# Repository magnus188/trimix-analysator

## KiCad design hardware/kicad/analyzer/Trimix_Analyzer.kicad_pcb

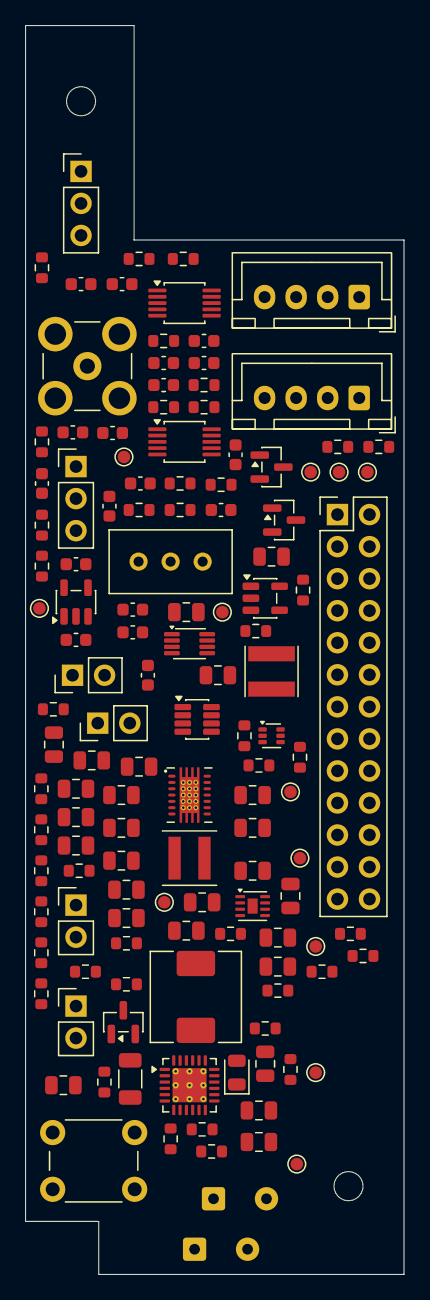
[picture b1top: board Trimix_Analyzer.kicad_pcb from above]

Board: 4 copper layers, 30.0 x 99.0 mm, 133 parts (0 on the bottom side), 67 nets, no tracks yet.

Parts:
C101: 1u / 25V X7R; C_0805_2012Metric
C102: 10u / 25V X7R; C_1206_3216Metric
C103: 47n / 16V X7R; C_0805_2012Metric
C104, C105, C204, C205, C206: 22u / 10V X7R; C_0805_2012Metric
C106, C201, C202: 10u / 10V X7R; C_0805_2012Metric
C107: 4.7u / 10V X7R; C_0805_2012Metric
C203, C301: 100n / 10V X7R; C_0805_2012Metric
C401, C404, C408, C409, C505, C509: 1u / X7R; C_0603_1608Metric
C402, C403, C405, C406, C503, C506, C507: 10n; C_0603_1608Metric
C407, C504, C508: 100n; C_0603_1608Metric
C501, C502: 4.7u / X7R / 10V; C_0603_1608Metric
C601, C804: 1u / 10V; C_0805_2012Metric
C701: 10u / 10V; C_0805_2012Metric
C702, C703: 22u / 10V; C_0805_2012Metric
C704, C705: 4.7u / 10V; C_0805_2012Metric
C706: 10n; C_0805_2012Metric
C707, C708: 100n; C_0805_2012Metric
C801, C802: 100n / 10V; C_0805_2012Metric
C803: 33n / 10V; C_0805_2012Metric
D101: CHARGE (red); LED_0805_2012Metric
H1, H2: M2 NPTH 2.30; Mechanical_M2_NPTH_2.30mm
J101: FROM USB BOARD (2P); SolderWire-0.25sqmm_1x02_P4.2mm_D0.65mm_OD1.7mm
J102: PACK PIGTAIL; SolderWire-0.25sqmm_1x02_P4.2mm_D0.65mm_OD1.7mm
J103: PACK NTC: 103AT-2; PinHeader_1x02_P2.54mm_Vertical
J104: ARM: OPEN; PinHeader_1x02_P2.54mm_Vertical
J301: GUITION JP1 / 2x13; PinHeader_2x13_P2.54mm_Vertical
J401: AO2 / 3-pin cable; PinHeader_1x03_P2.54mm_Vertical
J402: SMB Male PCB / verify fit; SMB_Jack_Vertical
J501: MD62 cable / <=30 cm; PinHeader_1x03_P2.54mm_Vertical
J601: BME280 harness; JST_XH_B4B-XH-A_1x04_P2.50mm_Vertical
J701: ZE07-CO harness; JST_XH_B4B-XH-A_1x04_P2.50mm_Vertical
J801: POWER BUTTON / 1NO; PinHeader_1x02_P2.54mm_Vertical
J802: BUTTON LED +/-; PinHeader_1x02_P2.54mm_Vertical
L101: 1u / Isat >= 4.5A; L_Wuerth_HCM-7050
L201: 1.5u / XFL4020-152ME; L_Coilcraft_XxL4020
L701: 1uH / Isat >= 5 A; L_Taiyo-Yuden_NR-40xx
Q101: 2N7002; SOT-23
Q601, Q602: BSS138; SOT-23
R101: 5.23k 1%; R_0603_1608Metric
R102: 30.1k 1%; R_0603_1608Metric
R103: 620R 1%; R_0603_1608Metric
R104, R105, R203, R501, R703, R803: 100k; R_0603_1608Metric
R106: 2.2k; R_0603_1608Metric
R107, R301, R802: 10k; R_0603_1608Metric
R201: 1.62M 1%; R_0603_1608Metric
R202: 180k 1%; R_0603_1608Metric
R302, R303: 4.7k / FIT; R_0603_1608Metric
R401, R402, R405, R406, R506, R507: 100R / 0.1%; R_0603_1608Metric
R403, R404, R407, R408: 1M / 1%; R_0603_1608Metric
R409, R410, R504, R505: 10k / 0.1%; R_0603_1608Metric
R502, R503: 2k / 0.1%; R_0603_1608Metric
R601: 0R / fit: 3.3 V; R_0603_1608Metric
R602: 0R / DNP: 5 V option; R_0603_1608Metric
R603, R604: 4.7k / DNP; R_0603_1608Metric
R701: 787k / 0.1%; R_0603_1608Metric
R702: 100k / 0.1%; R_0603_1608Metric
R704, R705: 100R; R_0603_1608Metric
R801: 5.1k; R_0603_1608Metric
R804: 1k / DNP; R_0603_1608Metric
RV501: 500R / multiturn; Potentiometer_Bourns_3296W_Vertical
SW101: BQ wake / reset; SW_PUSH_6mm
TP1001: GND; TestPoint_Pad_D1.0mm
TP1002: USB_5V; TestPoint_Pad_D1.0mm
TP1003: PACK_P; TestPoint_Pad_D1.0mm
TP1004: VSYS; TestPoint_Pad_D1.0mm
TP1005: VOUT_5V; TestPoint_Pad_D1.0mm
TP1006: HOST_3V3; TestPoint_Pad_D1.0mm
TP1007: POWER_EN; TestPoint_Pad_D1.0mm
TP1008: I2C_SCL; TestPoint_Pad_D1.0mm
TP1009: I2C_SDA; TestPoint_Pad_D1.0mm
TP1010: HE_3V0; TestPoint_Pad_D1.0mm
TP1011: HE_SENSE; TestPoint_Pad_D1.0mm
TP1012: O2_VMID; TestPoint_Pad_D1.0mm
U101: BQ25895RTWR; Texas_RTW_WQFN-24-1EP_4x4mm_P0.5mm_EP2.7x2.7mm_ThermalVias
U201: TPS63020DSJR; TI_DSJ_14
U301: MAX17048G+; TDFN-8-1EP_2x2mm_P0.5mm_EP0.8x1.2mm
U401, U502: ADS1115IDGS; TSSOP-10_3x3mm_P0.5mm
U501, U702: SPX3819M5-L-3-0; SOT-23-5
U701: TPS61023DRLR; SOT-563
U703: TXU0202DCUR; VSSOP-8_2.3x2mm_P0.5mm
U801: LTC2954CTS8-1; TSOT-23-8

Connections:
/01 CHARGING + BATTERY/BQ_BTST: C103.2, U101.21
/01 CHARGING + BATTERY/BQ_ILIM: R103.1, U101.10
/01 CHARGING + BATTERY/BQ_PMID: C102.1, U101.23
/01 CHARGING + BATTERY/BQ_QON_N: SW101.1, U101.12
/01 CHARGING + BATTERY/BQ_REGN: C107.1, R101.1, U101.22
/01 CHARGING + BATTERY/BQ_SW: C103.1, L101.1, U101.19, U101.20
/01 CHARGING + BATTERY/CHG_CE_N: Q101.3, R104.2, U101.9
/01 CHARGING + BATTERY/CHG_STAT_N: D101.1, U101.4
/01 CHARGING + BATTERY/PACK_TS: J103.1, R101.2, R102.1, U101.11
/02 SWITCHED 5 V/TPS_FB: R201.2, R202.1, U201.3
/02 SWITCHED 5 V/TPS_VINA: C203.1, U201.1
BME_SCL: J601.3, Q601.3, R603.2
BME_SDA: J601.4, Q602.3, R604.2
BME_VIN: C601.1, J601.1, R601.2, R602.2, R603.1, R604.1
BUTTON_LED_A: J802.1, R804.2
CHARGE_ARM: J104.2, Q101.1, R105.1
CHG_INT_N: J301.13, R107.2, U101.7
CO_5V28: C702.1, C703.1, J701.1, R701.1, U701.6
CO_FB: R701.2, R702.1, U701.1
CO_LOGIC_3V0: C705.1, C708.1, U702.5, U703.7
CO_LOGIC_BYP: C706.1, U702.4
CO_RX_3V0: R705.1, U703.8
CO_RX_CABLE: J701.4, R705.2
CO_SW: L701.2, U701.5
CO_TX_3V0: R704.1, U703.1
CO_TX_CABLE: J701.3, R704.2
CO_UART_EN: J301.9, R703.1, U703.6
CO_UART_RX: J301.10, U703.4
CO_UART_TX: J301.12, U703.5
GAUGE_ALERT_N: J301.11, R301.2, U301.5
GND: C101.2, C102.2, C104.2, C105.2, C106.2, C107.2, C201.2, C202.2, C203.2, C204.2, C205.2, C206.2, C301.2, C402.2, C403.2, C405.2, C406.2, C407.2, C408.2, C409.2, C501.2, C502.2, C503.2, C504.2, C506.2, C507.2, C508.2, C509.2, C601.2, C701.2, C702.2, C703.2, C704.2, C705.2, C706.2, C707.2, C708.2, C801.2, C802.2, C803.2, C804.2, J101.2, J102.2, J103.2, J301.5, J301.6, J301.16, J501.3, J601.2, J701.2, J801.2, J802.2, Q101.2, R102.2, R103.2, R105.2, R202.2, R410.2, R501.2, R503.2, R505.2, R702.2, R703.2, SW101.2, TP1001.1, U101.8, U101.17, U101.18, U101.25, U201.2, U201.15, U301.1, U301.4, U301.6, U301.9, U401.1, U401.3, U501.2, U502.3, U701.4, U702.2, U703.2, U801.4
HE_3V0: C502.1, J501.1, R502.1, R504.1, TP1010.1, U501.5
HE_AIN_N: C505.2, C507.1, R507.2, U502.5
HE_AIN_P: C505.1, C506.1, R506.2, U502.4
HE_ENABLE: J301.17, R501.1, U501.3
HE_EXC_DIV: C504.1, R504.2, R505.1, U502.6
HE_REF: R506.1, RV501.2
HE_SENSE: J501.2, R507.1, TP1011.1
HOST_3V3: C407.1, C408.1, C508.1, C509.1, C707.1, J301.1, J301.3, J301.18, Q601.1, Q602.1, R107.1, R301.1, R302.1, R303.1, R409.1, R601.1, R802.1, R803.1, TP1006.1, U401.8, U502.1, U502.8, U703.3
I2C_SCL: J301.14, Q601.2, R302.2, TP1008.1, U101.5, U301.7, U401.10, U502.10
I2C_SDA: J301.21, Q602.2, R303.2, TP1009.1, U101.6, U301.8, U401.9, U502.9
unnamed: D101.2, R106.1
unnamed: J801.1, R801.1
unnamed: L201.1, U201.8, U201.9
unnamed: L201.2, U201.6, U201.7
unnamed: R502.2, RV501.1
unnamed: R503.1, RV501.3
unnamed: C503.1, U501.4
unnamed: C803.1, U801.3
unnamed: C804.1, U801.7
O2_A_AIN_N: C401.1, C402.1, R401.2, R403.1, U401.5
O2_A_AIN_P: C401.2, C403.1, R402.2, R404.2, U401.4
O2_A_RAW_N: J401.2, R401.1
O2_A_RAW_P: J401.1, R402.1
O2_B_AIN_N: C404.1, C405.1, R405.2, R407.1, U401.7
O2_B_AIN_P: C404.2, C406.1, R406.2, R408.2, U401.6
O2_B_RAW_N: J402.2, R405.1
O2_B_RAW_P: J402.1, R406.1
O2_VMID: C409.1, R403.2, R404.1, R407.2, R408.1, R409.2, R410.1, TP1012.1, U502.7
PACK_P: C106.1, C301.1, J102.1, TP1003.1, U101.13, U101.14, U301.2, U301.3
PB_FILTERED_N: C802.1, R801.2, U801.2
POWER_EN: R203.2, TP1007.1, U201.12, U801.6
POWER_INT_N: J301.19, R802.2, U801.5
POWER_KILL_N: J301.8, R803.2, U801.8
USB_5V: C101.1, J101.1, TP1002.1, U101.1
VOUT_5V: C204.1, C205.1, C206.1, C501.1, C701.1, C704.1, J301.2, J301.4, L701.1, R201.1, R602.1, R804.1, TP1005.1, U201.4, U201.5, U501.1, U701.2, U701.3, U702.1, U702.3
VSYS: C104.1, C105.1, C201.1, C202.1, C801.1, J104.1, L101.2, R104.1, R106.2, R203.1, TP1004.1, U101.15, U101.16, U201.10, U201.11, U201.13, U801.1

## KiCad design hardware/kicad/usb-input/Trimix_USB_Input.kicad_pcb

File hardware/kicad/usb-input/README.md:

# GCT USB input daughterboard — A2.2

Open `Trimix_USB_Input.kicad_pro`. This is the same circuit shown on page 10
of the complete analyser, with its four parts included for a separate PCB.

- J901: GCT USB4720-03-A, selected replacement connector.
- R901/R902: fit 5.1 kΩ 1% on CC1/CC2 independently.
- J902: soldered two-wire output to main PCB J101, pin 1 positive and pin 2 GND.

Use 0.60 ±0.10 mm PCB thickness per the manufacturer drawing. The main board
stays 1.60 mm. This project has a checked schematic and a drawing-based
connector land pattern; final PCB outline, routing, mechanical support and
enclosure sealing have not been completed. The footprint cutout lines on
Dwgs.User are a guide, not fabrication Edge.Cuts. No exact STEP model is
attached. Do not order the unfinished PCB.

See `../../USB_CHARGING.md` for source references and physical tests.

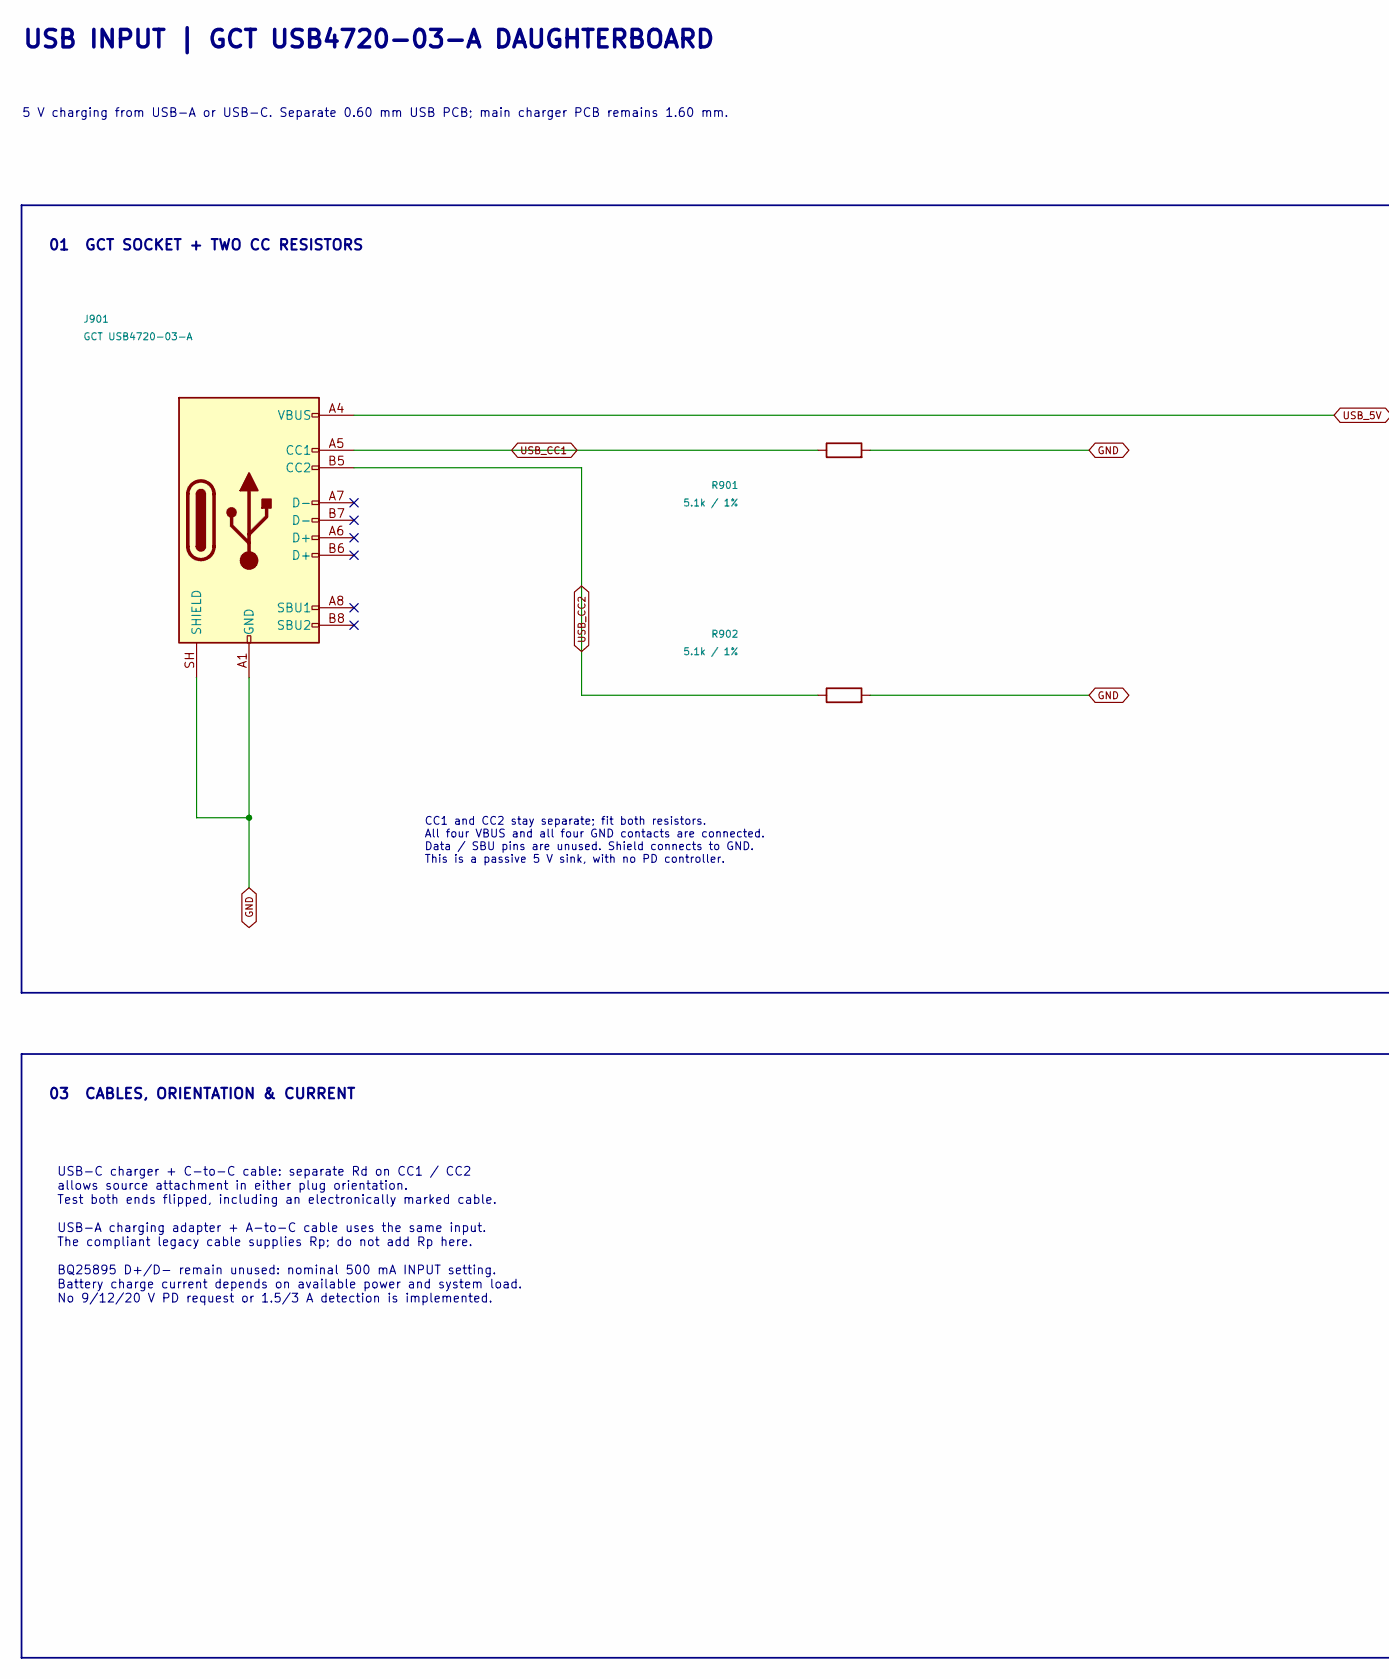
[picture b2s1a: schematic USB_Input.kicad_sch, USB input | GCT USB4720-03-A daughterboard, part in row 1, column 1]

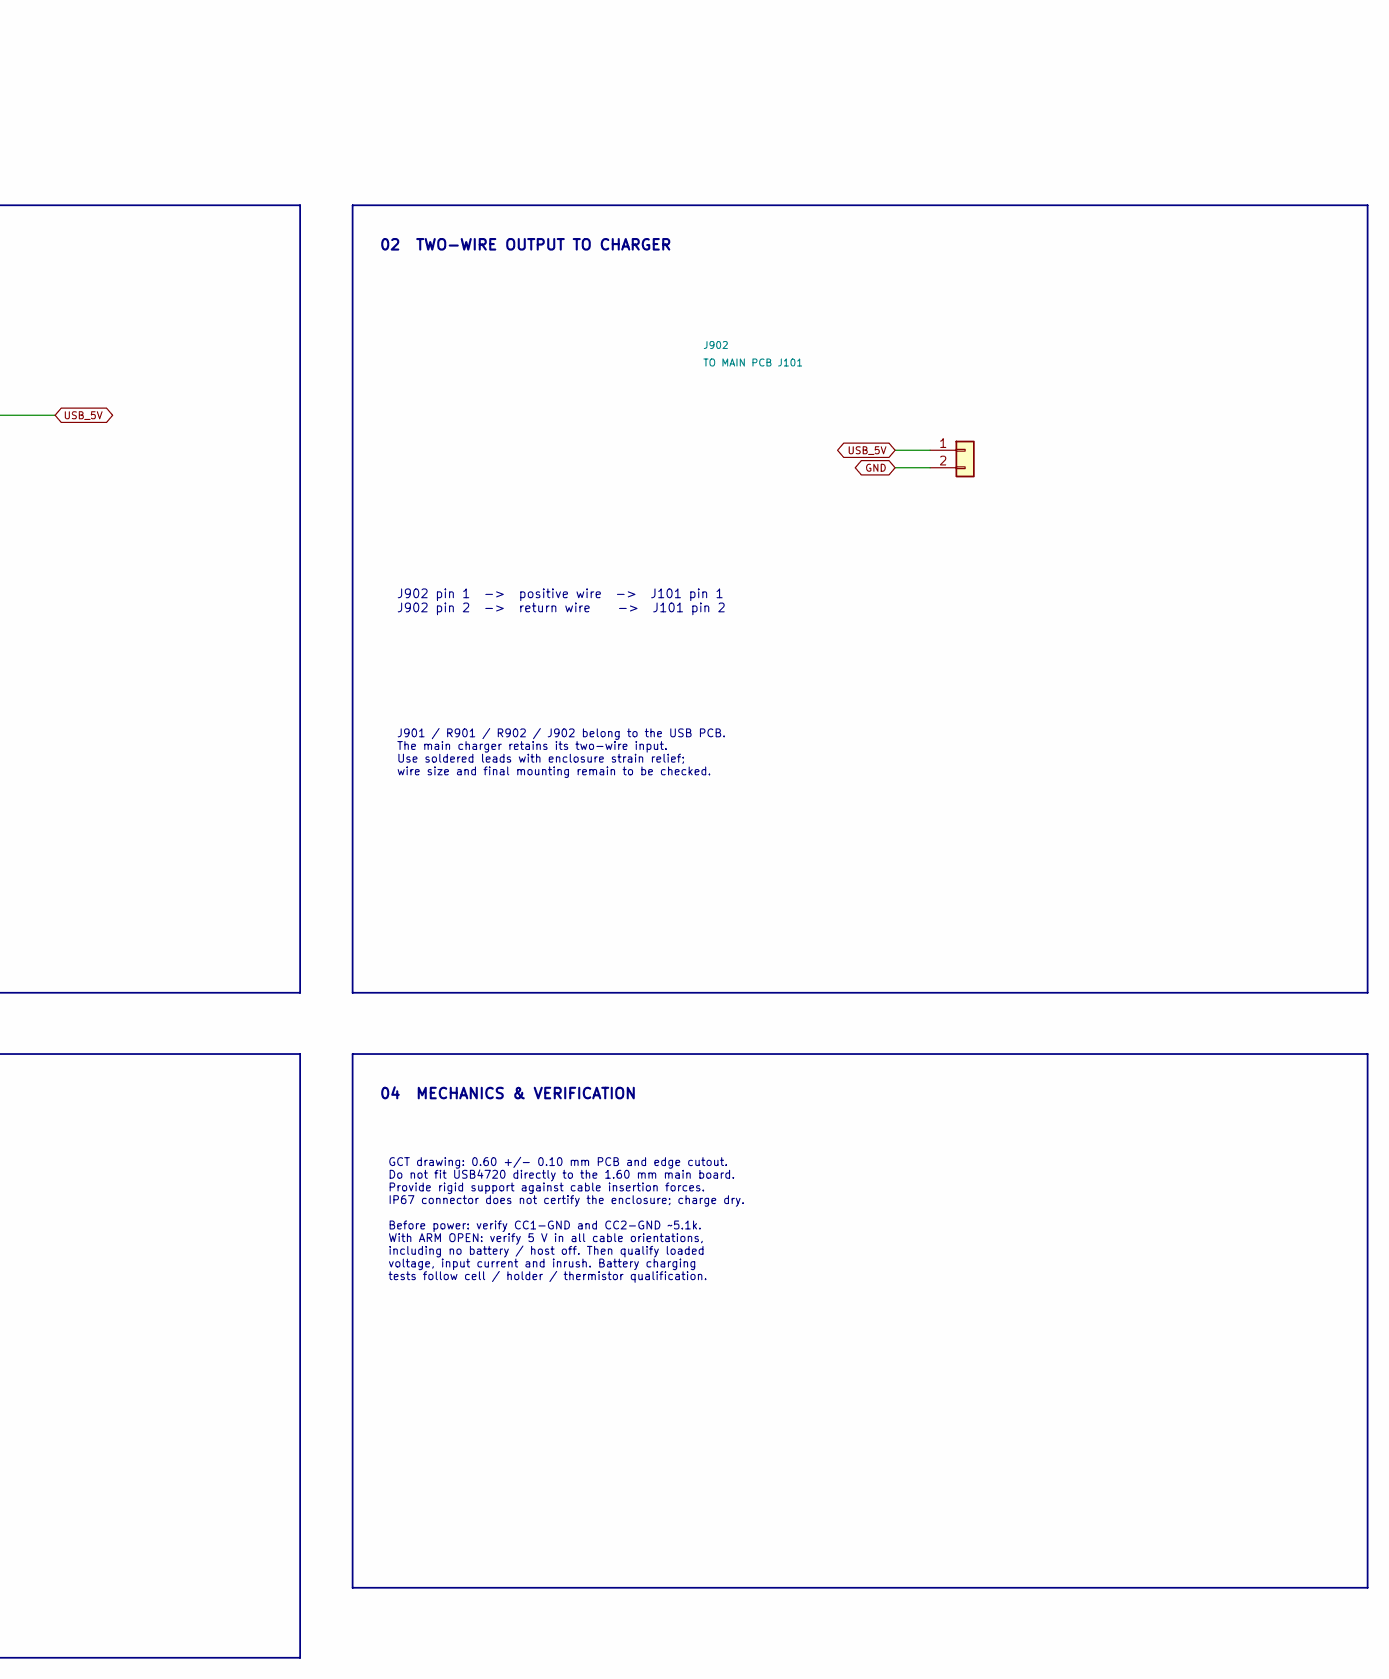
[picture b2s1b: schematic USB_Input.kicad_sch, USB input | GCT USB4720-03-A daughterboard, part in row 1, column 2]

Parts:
J901: GCT USB4720-03-A; USB_C_GCT_USB4720-03-A_A3; MPN USB4720-03-A
J902: TO MAIN PCB J101; SolderWire-0.25sqmm_1x02_P4.2mm_D0.65mm_OD1.7mm
R901, R902: 5.1k / 1%; R_0603_1608Metric

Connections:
GND: J901.A1 (GND), J901.A12 (GND), J901.B1 (GND), J901.B12 (GND), J901.SH (SHIELD), J902.2, R901.2, R902.2
USB_5V: J901.A4 (VBUS), J901.A9 (VBUS), J901.B4 (VBUS), J901.B9 (VBUS), J902.1
USB_CC1: J901.A5 (CC1), R901.1
USB_CC2: J901.B5 (CC2), R902.1

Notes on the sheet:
USB INPUT | GCT USB4720-03-A DAUGHTERBOARD
5 V charging from USB-A or USB-C. Separate 0.60 mm USB PCB; main charger PCB remains 1.60 mm.
01 GCT SOCKET + TWO CC RESISTORS
02 TWO-WIRE OUTPUT TO CHARGER
03 CABLES, ORIENTATION & CURRENT
04 MECHANICS & VERIFICATION
CC1 and CC2 stay separate; fit both resistors. All four VBUS and all four GND contacts are connected. Data / SBU pins are unused. Shield connects to GND. This is a passive 5 V sink, with no PD controller.
J902 pin 1 -> positive wire -> J101 pin 1 J902 pin 2 -> return wire -> J101 pin 2
J901 / R901 / R902 / J902 belong to the USB PCB. The main charger retains its two-wire input. Use soldered leads with enclosure strain relief; wire size and final mounting remain to be checked.
USB-C charger + C-to-C cable: separate Rd on CC1 / CC2 allows source attachment in either plug orientation. Test both ends flipped, including an electronically marked cable. USB-A charging adapter + A-to-C cable uses the same input. The compliant legacy cable supplies Rp; do not add Rp here. BQ2589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
GCT drawing: 0.60 +/- 0.10 mm PCB and edge cutout. Do not fit USB4720 directly to the 1.60 mm main board. Provide rigid support against cable insertion forces. IP67 connector does not certify the enclosure; charge dry. Before power: verify CC1-GND and CC2-GND ~5.1k. With ARM OPEN: verify 5 V in all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

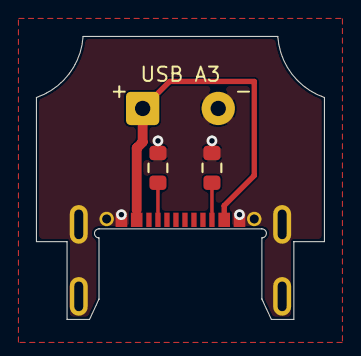
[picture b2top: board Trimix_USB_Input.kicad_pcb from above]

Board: 2 copper layers, 16.0 x 15.7 mm, 4 parts (0 on the bottom side), 4 nets.
